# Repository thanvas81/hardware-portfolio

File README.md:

# Hardware Portfolio

PCB and embedded hardware projects by **Athanasios Vasiloglou**, Embedded Systems & Hardware Engineer.

Each project has 3D renders, schematics, layer views where available, and a write-up of the design. Projects are listed from most to least complex.

## At a glance

| # | Project | Area | Board | Key parts |
|---|---|---|---|---|
| 1 | [Industrial Controller / Gateway](industrial-controller-gateway/) | Industrial control | 4-layer · 340 × 147 mm · 486 parts | STM32H743, KSZ8863 Ethernet switch, isolated RS-485, mains AC/DC |
| 2 | [Linux SoM Carrier Board](linux-som-carrier-board/) | Industrial IoT | 4-layer · 167 × 100 mm · 274 parts | i.MX 91 SoM, EC25 LTE, Ethernet, RS-485, CAN |
| 3 | [Handheld High-Irradiance LED Controller](handheld-irradiance-system/) | Power electronics | 3 boards · Altium | USB-C PD, 2S charger, 4-switch buck-boost, nRF52840 |
| 4 | [GPS/GSM Tracker (Rev 3)](gps-gsm-tracker/) | IoT & tracking | 4-layer · 65 × 94 mm · 192 parts | STM32U575, LTE Cat-1, NEO-M9N GNSS |
| 5 | [BLE Channel Sounding Sensor Board](ble-channel-sounding-board/) | Wireless / thesis | 4-layer · 38 × 25 mm | nRF54L15, Channel Sounding, 17 cm mean error |
| 6 | [Vehicle I/O Validator (Rev 2)](vehicle-io-validator/) | Automotive test | 4-layer · 142 × 72 mm · 232 parts | STM32U545, 20 protected inputs, USB-C |
| 7 | [Compact LTE-M / NB-IoT Tracker](compact-lte-tracker/) | IoT & tracking | 4-layer · 49 × 53 mm · 89 parts | BG96, STM32U545, Li-ion charger |
| 8 | [Control Unit Tester (Rev 2)](control-unit-tester/) | Automotive test | 4-layer · 194 × 52 mm · 236 parts | Window comparators, 20 switched outputs |
| 9 | [RP2040 Diagnostic Tester (Rev 2)](rp2040-diagnostic-tester/) | Test tools | 2-layer · 69 × 54 mm | Raspberry Pi Pico, UART sniffer, 24 V input |
| 10 | [CANLink Module](can-link-module/) | Expansion module | 2-layer · 65 × 64 mm | PIC18 CAN controller, TCAN3413 |
| 11 | [Relay & Analog Input Expansion Board](relay-analog-io-board/) | Expansion module | 2-layer · 65 × 38 mm | TX2 relay, LMV324 analog front end |

---

## Featured projects

### [Industrial Controller / Gateway](industrial-controller-gateway/)

Mains-powered controller bridging a managed Ethernet switch to 24 V field I/O.

- STM32H743, KSZ8863 2-port Ethernet switch
- 2× isolated RS-485, 4–20 mA, PT100, opto inputs, relays, smart high-side outputs
- On-board 90 W AC/DC, four isolation domains, mains relay channel
- 4-layer, 340 × 147 mm, 486 components

`STM32H7` `Ethernet` `Isolation` `Mains` `KiCad`

<br clear="right">

---

### [Linux SoM Carrier Board](linux-som-carrier-board/)

Industrial IoT carrier for an NXP i.MX 91 Linux SoM. Full design and bring-up.

- Quectel EC25 LTE (mini-PCIe), dual SIM
- Ethernet, RS-485, CAN, USB-C, digital I/O, RTC, tamper input
- Wide-input supply, Li-ion backup with power-path
- 4-layer, 167 × 100 mm, 274 components

`i.MX 91` `Embedded Linux` `LTE` `KiCad` `Industrial IoT`

<br clear="right">

---

### [Handheld High-Irradiance LED Controller](handheld-irradiance-system/)

Battery-powered controller for a high-power red LED array. Freelance design across three boards.

- USB-C PD input, 2S Li-ion charger with power-path
- 4-switch buck-boost LED rail, 7 constant-current channels
- nRF52840 Bluetooth LE, IR temperature sensing, fan control

`Altium` `USB-C PD` `Power electronics` `nRF52840` `LED drivers`

<br clear="right">

---

### [GPS/GSM Tracker](gps-gsm-tracker/)

LTE Cat-1 + GNSS vehicle tracker, Rev 3 redesigned in KiCad for production.

- STM32U575 low-power MCU, SIMCom A7672 LTE modem, u-blox NEO-M9N GNSS
- Li-ion charger with power-path, wide-input buck, backup cell
- 4-layer, 65 × 94 mm, 192 components

`STM32U5` `LTE Cat-1` `GNSS` `KiCad` `4-layer`

<br clear="right">

---

### [BLE Channel Sounding Sensor Board](ble-channel-sounding-board/)

Custom nRF54L15 board for sub-metre indoor positioning with Bluetooth Channel Sounding. NTUA diploma thesis.

- **17 cm** mean ranging error across three anchors
- 4-layer, 38 × 25 mm PCB in KiCad
- Accelerometer + magnetometer, temperature / humidity / pressure
- USB-C or Li-ion, with charger and buck-boost

`nRF54L15` `Zephyr` `KiCad` `BLE` `Channel Sounding`

<br clear="right">

---

### [Vehicle I/O Validator](vehicle-io-validator/)

Test tool that monitors 20 vehicle I/O lines and reports them to a PC over USB.

- 20 protected inputs with red / blue status LEDs per channel
- STM32U545, USB-C, 60 V buck from the vehicle supply
- 4-layer, 142 × 72 mm, 232 components

`STM32U5` `Automotive` `Test equipment` `KiCad`

<br clear="right">

---

### [Compact LTE-M / NB-IoT Tracker](compact-lte-tracker/)

Small battery-backed asset tracker.

- Quectel BG96 (LTE-M / NB-IoT + GNSS), STM32U545
- Accelerometer wake-up, NOR flash logging
- Li-ion charger, wide-input buck, switched modem rail
- 4-layer, 49 × 53 mm, 89 components

`STM32U5` `LTE-M` `NB-IoT` `GNSS` `KiCad`

<br clear="right">

---

### [Control Unit Tester](control-unit-tester/)

Stand-alone, fully analog bench tester for vehicle control units.

- 16 inputs with window-comparator status LEDs
- 20 outputs, each switchable to +Vin / open / GND
- 60 V buck from the vehicle supply, no MCU needed
- 4-layer, 194 × 52 mm, 236 components

`Analog` `Automotive` `Test equipment` `KiCad`

<br clear="right">

---

## More boards

| | |
|:---:|:---:|
| <br>**[RP2040 Diagnostic Tester](rp2040-diagnostic-tester/)**<br>Raspberry Pi Pico field tool that talks to and sniffs UART links on 24 V equipment, with LCD and buttons | <br>**[CANLink Module](can-link-module/)**<br>Plug-in CAN ↔ UART bridge: PIC18 with on-chip CAN controller and TI TCAN3413 transceiver |
| <br>**[Relay & Analog Input Expansion Board](relay-analog-io-board/)**<br>Stack-on board with a relay output and protected, buffered analog inputs | |

---

[LinkedIn](https://www.linkedin.com/in/athanasios-vasiloglou-424599182/) · [GitHub profile](https://github.com/thanvas81)

<sub>Designs are shown for portfolio purposes only. Projects built for employers and clients are presented without source files, and are not licensed for reuse.</sub>

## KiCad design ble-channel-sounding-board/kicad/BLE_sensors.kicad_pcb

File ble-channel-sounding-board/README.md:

# BLE Channel Sounding Sensor Board

**Custom nRF54L15 board for sub-metre indoor positioning with Bluetooth Channel Sounding, plus environmental and motion sensing.**

Diploma thesis, School of Electrical and Computer Engineering, National Technical University of Athens (2025).
*Design of a Wireless Indoor Tracking System for Multi-Sensor Data Acquisition with BLE Channel Sounding*. Supervisor: Prof. E. Hristoforou.

<p align="center">
  
  &nbsp;
  
</p>

## Highlights

- **17 cm mean ranging error** across three anchors at 3–4.5 m, measured over a one-hour indoor capture
- **Bluetooth Channel Sounding** (Bluetooth 6.0) distance estimation using IFFT and phase-based ranging, instead of RSSI
- **4-layer, 38 × 25 mm PCB** designed in KiCad around the nRF54L15 SoC, with a continuous inner ground plane for RF performance
- **Multi-sensor**: 3-axis accelerometer + magnetometer (motion wake-up) and temperature / humidity / pressure
- **Portable power**: USB-C or single-cell Li-ion, with charger, power-path and buck-boost to a stable 3.3 V

## System overview

```mermaid
flowchart LR
    subgraph Tag["Tag (reflector) – this board"]
        S1["LSM303AH<br/>accel + magnetometer"] -->|SPI| MCU["nRF54L15<br/>(ME54BS01 module)"]
        S2["BME280<br/>temp / humidity / pressure"] -->|I²C| MCU
        PWR["USB-C / Li-ion<br/>charger + buck-boost"] --> MCU
    end
    subgraph Anchors["Anchors (initiators)"]
        A1["Initiator 1"]
        A2["Initiator 2"]
        A3["Initiator 3"]
    end
    MCU <-->|"BLE Channel Sounding"| A1 & A2 & A3
    MCU -->|"BLE advertising<br/>sensor data"| A1
    A1 & A2 & A3 -->|"UART → USB"| PC["Host PC<br/>logging & visualisation"]
```

## Hardware

| Block | Part | Notes |
|---|---|---|
| SoC / radio | Minew **ME54BS01** (Nordic **nRF54L15**) | BLE 6.0 Channel Sounding, integrated antenna |
| Motion | ST **LSM303AH** | 3-axis accelerometer + magnetometer on SPI, interrupt lines for motion wake-up |
| Environment | Bosch **BME280** | Temperature, humidity, pressure on I²C |
| Charger | Microchip **MCP73871** | Li-ion charging with power-path management and NTC input |
| Regulation | TI **TPS63031** buck-boost, TI **TLV70018** LDO | 3.3 V from 3.0–4.2 V battery or 5 V USB |
| USB | USB-C receptacle, Nexperia **PRTR5V0U2X** ESD, Microchip **MCP2221A** | USB-to-UART bridge for logging |
| Debug | Tag-Connect **TC2030** | SWD programming without a header |

Schematic is split into hierarchical sheets: power supply, charger, buck-boost, LDO, USB-C, USB-to-serial, temperature sensor, accelerometer/magnetometer.

**Files**

### PCB layers

4-layer stackup, 1.6 mm FR4: signals on the outer layers, a continuous ground plane on inner 1 for RF stability and clean return paths, and 3.3 V / 5 V power on inner 2.

| Top copper | Inner 1: ground plane |
|---|---|
|  |  |
| **Inner 2: power plane (3.3 V / 5 V)** | **Bottom copper** |
|  |  |

### Files

- [Schematic (PDF)](schematics/BLE_sensors_schematic.pdf)
- [Bill of materials](fabrication/BLE_sensors_BOM.xlsx)
- [Gerbers for fabrication](fabrication/BLE_sensors_gerbers.zip)
- [KiCad 9 project](kicad/): open `BLE_sensors.kicad_pro`

## Firmware

Written in C on **Zephyr RTOS / nRF Connect SDK** (source not included in this repository). Two roles:

**Tag (reflector)** – this board. Reads the sensors every 2 s, broadcasts them in non-connectable advertising, answers Channel Sounding requests, and sleeps when no motion is detected.

```mermaid
flowchart TD
    A["Start + init (BLE + sensors)"] --> B["Start advertising (CS reflector + data)"]
    B --> C["Every 2 s: read environment + battery"]
    C --> D["Send via non-connectable advertising"]
    B --> E["On connect → configure CS (reflector role)"]
    B --> G["Motion detected? → stay awake"]
    G --> H["No motion → sleep"]
    H --> I["Motion interrupt → wake & resume"]
```

**Anchor (initiator)**. Scans for the tag, connects, runs continuous Channel Sounding procedures, computes the distance and logs it over UART with the received sensor data.

```mermaid
flowchart TD
    A["Start → scan"] --> B{"Ranging peer?"}
    B -- no --> A
    B -- yes --> C["Connect → discover → CS capabilities"]
    C --> D["Configure CS + start continuous"]
    D --> E["Process ranging data"]
    E --> F["Log distance (2 s)"]
    F --> D
    C --> G["Subscribe custom data"]
    G --> H["Receive and log env/sensor data"]
    H --> G
```

## Results

Three initiators were mounted on the walls at 3.0 m, 4.0 m and 4.5 m from a stationary tag, and distances were logged for one hour.

| Anchor | Distance | Mean absolute error |
|---|---|---|
| Initiator 1 | 4.0 m | 0.142 m |
| Initiator 2 | 4.5 m | 0.177 m |
| Initiator 3 | 3.0 m | 0.193 m |
| **Overall** | | **0.171 m** |

<p align="center">
  
  &nbsp;
  
</p>

The IFFT-based estimator gave the most stable distance estimates. Full method and measurements are in the thesis.

## Documents

- [Thesis (PDF)](docs/thesis.pdf)
- [Presentation slides](docs/thesis_presentation.pptx)
- [Flowcharts (Mermaid sources)](docs/flowcharts/)

## Folder layout

```
images/        3D renders, copper layers, test setup, results
schematics/    schematic PDF
kicad/         KiCad 9 project (schematic sheets + PCB)
fabrication/   Gerbers and BOM
docs/          thesis, slides, flowchart sources
```

---

[← Back to all projects](../README.md)

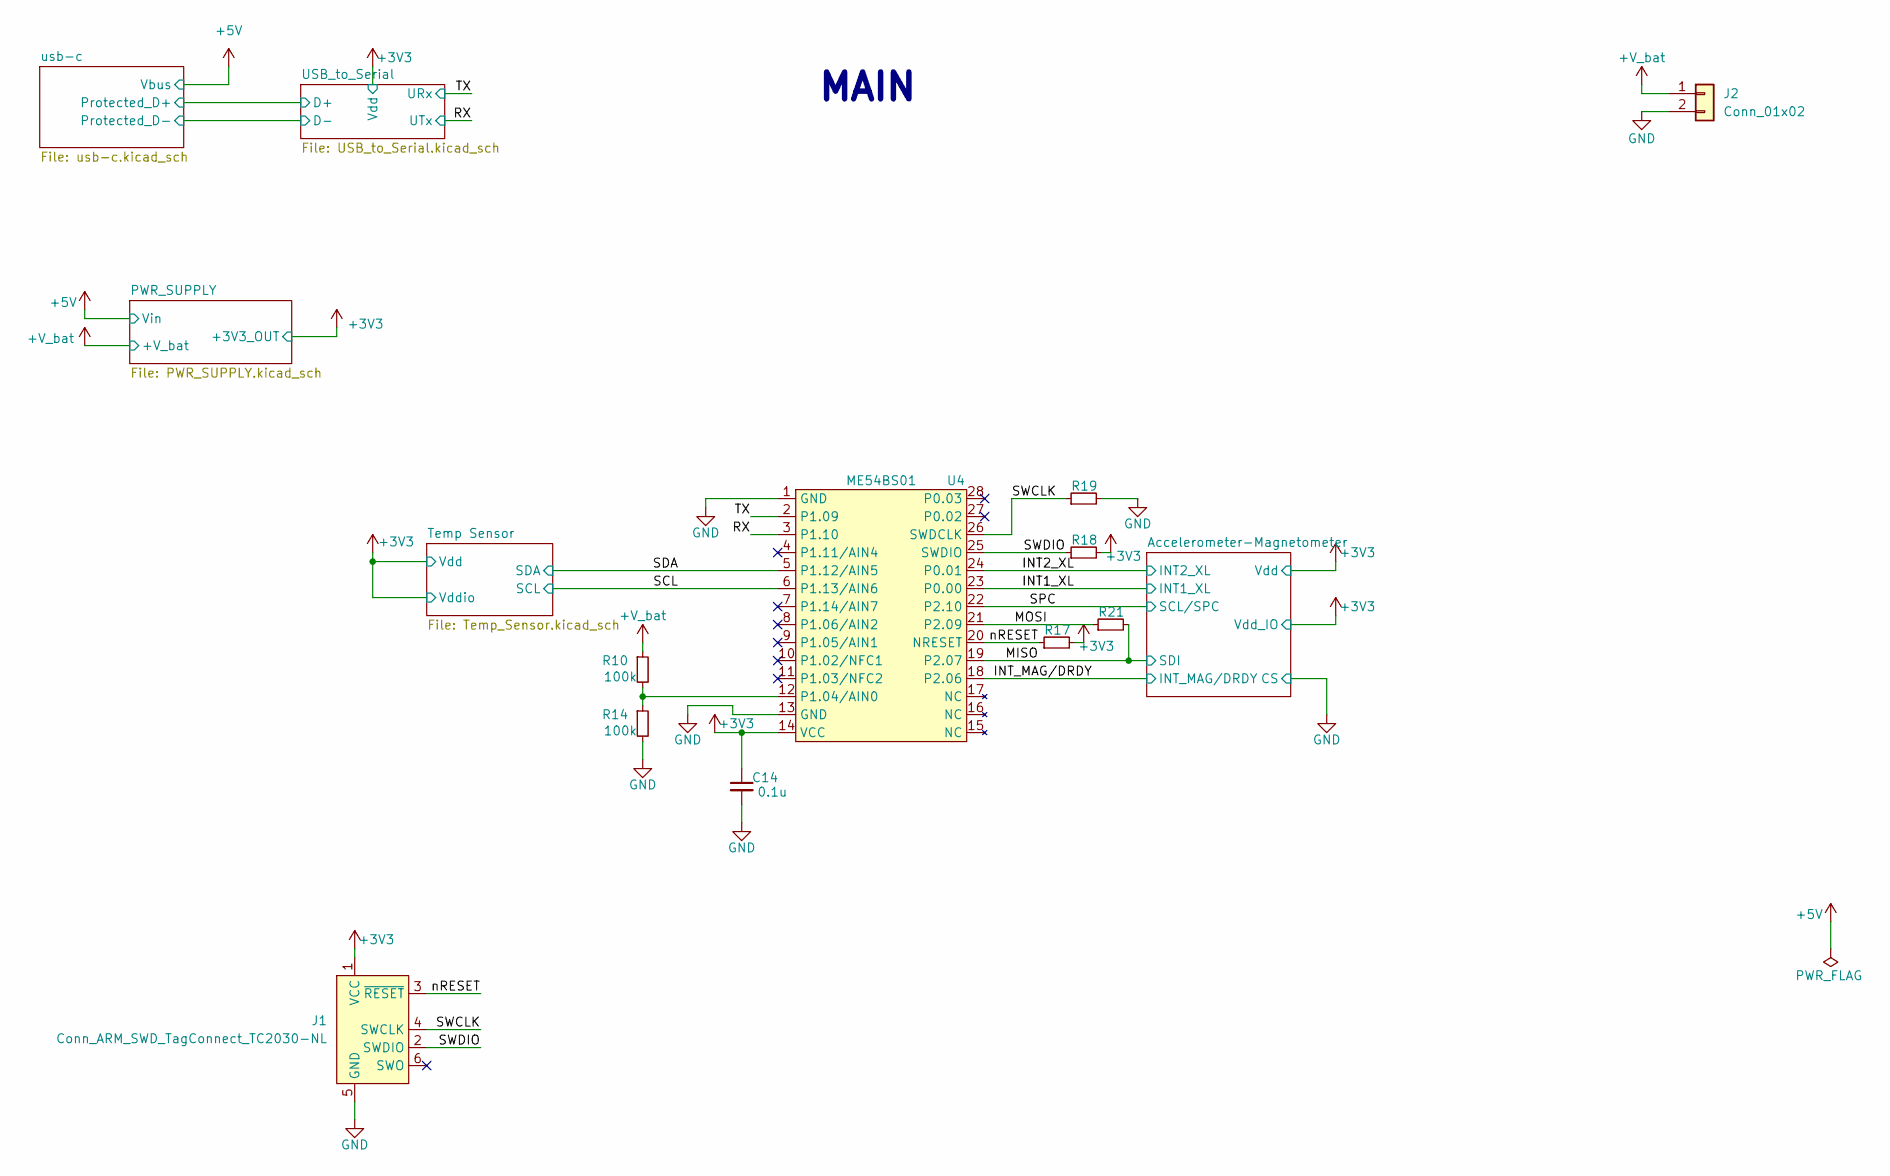
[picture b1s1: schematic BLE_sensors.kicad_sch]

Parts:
C14: 0.1u; C_0603_1608Metric
J1: Conn_ARM_SWD_TagConnect_TC2030-NL; Tag-Connect_TC2030-IDC-NL_2x03_P1.27mm_Vertical
J2: Conn_01x02; PinHeader_1x02_P1.27mm_Vertical
R10, R14: 100k; R_0603_1608Metric
R17, R18, R19, R21: 10k; R_0603_1608Metric
U4: ME54BS01

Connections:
+3V3: C14.1, J1.1 (VCC), R17.2, R18.2, U4.14 (VCC); also elsewhere on the board
+V_bat: J2.1, R10.1; also elsewhere on the board
/INT1_XL: U4.23 (P0.00); also elsewhere on the board
/INT2_XL: U4.24 (P0.01); also elsewhere on the board
/INT_MAG/DRDY: U4.18 (P2.06); also elsewhere on the board
/MISO: R21.2, U4.19 (P2.07); also elsewhere on the board
/MOSI: R21.1, U4.21 (P2.09)
/RX: U4.3 (P1.10); also elsewhere on the board
/SCL: U4.6 (P1.13/AIN6); also elsewhere on the board
/SDA: U4.5 (P1.12/AIN5); also elsewhere on the board
/SPC: U4.22 (P2.10); also elsewhere on the board
/SWCLK: J1.4 (SWCLK), R19.1, U4.26 (SWDCLK)
/SWDIO: J1.2 (SWDIO), R18.1, U4.25 (SWDIO)
/TX: U4.2 (P1.09); also elsewhere on the board
/nRESET: J1.3 (~RESET), R17.1, U4.20 (NRESET)
GND: C14.2, J1.5 (GND), J2.2, R14.2, R19.2, U4.1 (GND), U4.13 (GND); also elsewhere on the board
unnamed: R10.2, R14.1, U4.12 (P1.04/AIN0)

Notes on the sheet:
MAIN

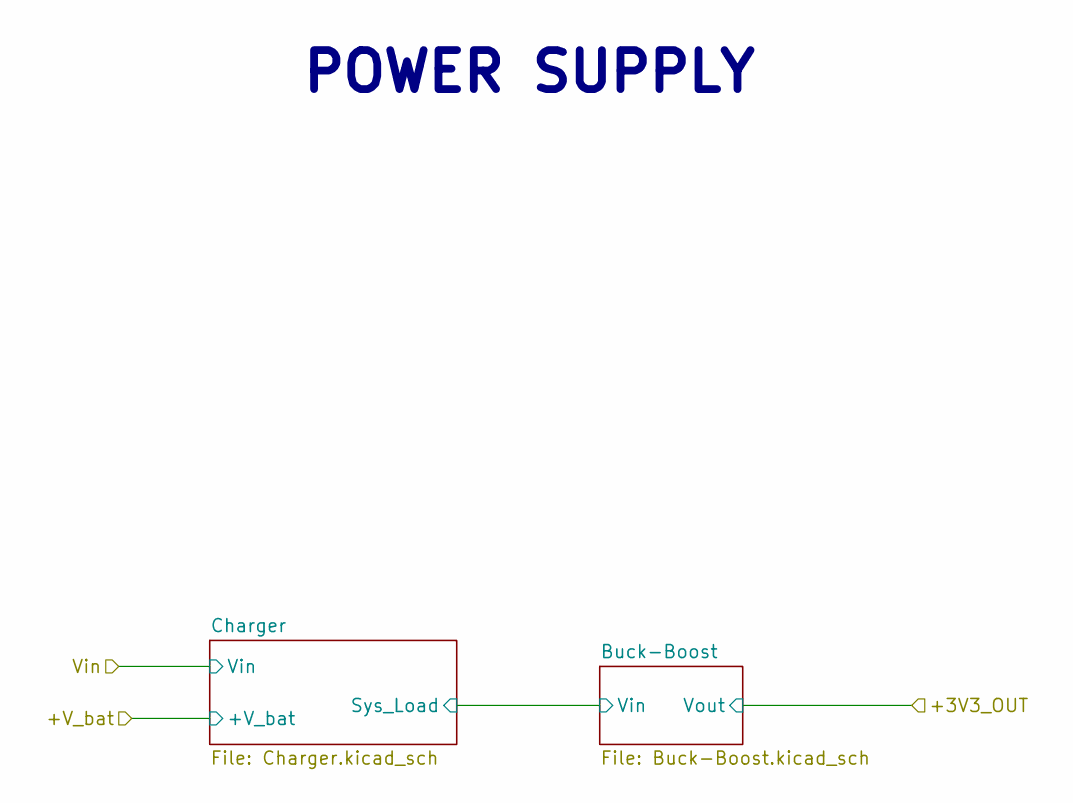
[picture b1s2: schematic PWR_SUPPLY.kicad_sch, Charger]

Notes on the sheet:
POWER SUPPLY

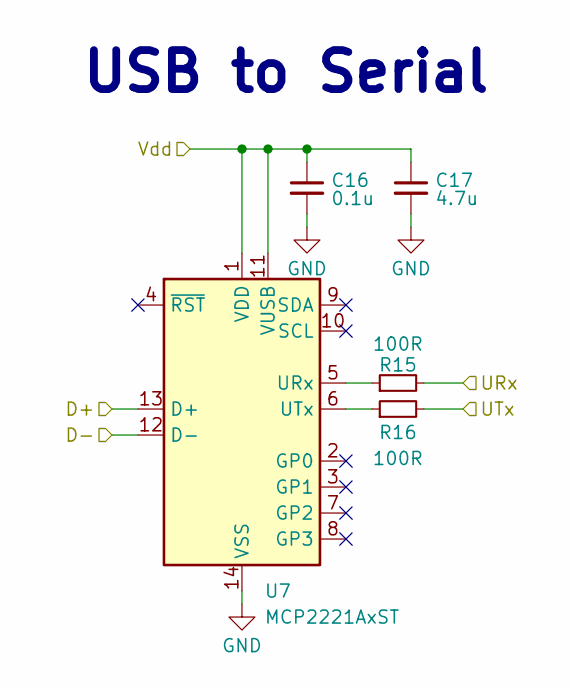
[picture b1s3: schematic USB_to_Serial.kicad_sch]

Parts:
C16: 0.1u; C_0603_1608Metric
C17: 4.7u; C_0805_2012Metric
R15, R16: 100R; R_0603_1608Metric
U7: MCP2221AxST; TSSOP-14_4.4x5mm_P0.65mm

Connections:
+3V3: C16.1, C17.1, U7.1 (VDD), U7.11 (VUSB); also elsewhere on the board
/RX: R16.2; also elsewhere on the board
/TX: R15.2; also elsewhere on the board
/usb-c/Protected_D+: U7.13 (D+); also elsewhere on the board
/usb-c/Protected_D-: U7.12 (D-); also elsewhere on the board
GND: C16.2, C17.2, U7.14 (VSS); also elsewhere on the board
unnamed: R15.1, U7.5 (URx)
unnamed: R16.1, U7.6 (UTx)

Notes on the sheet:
USB to Serial

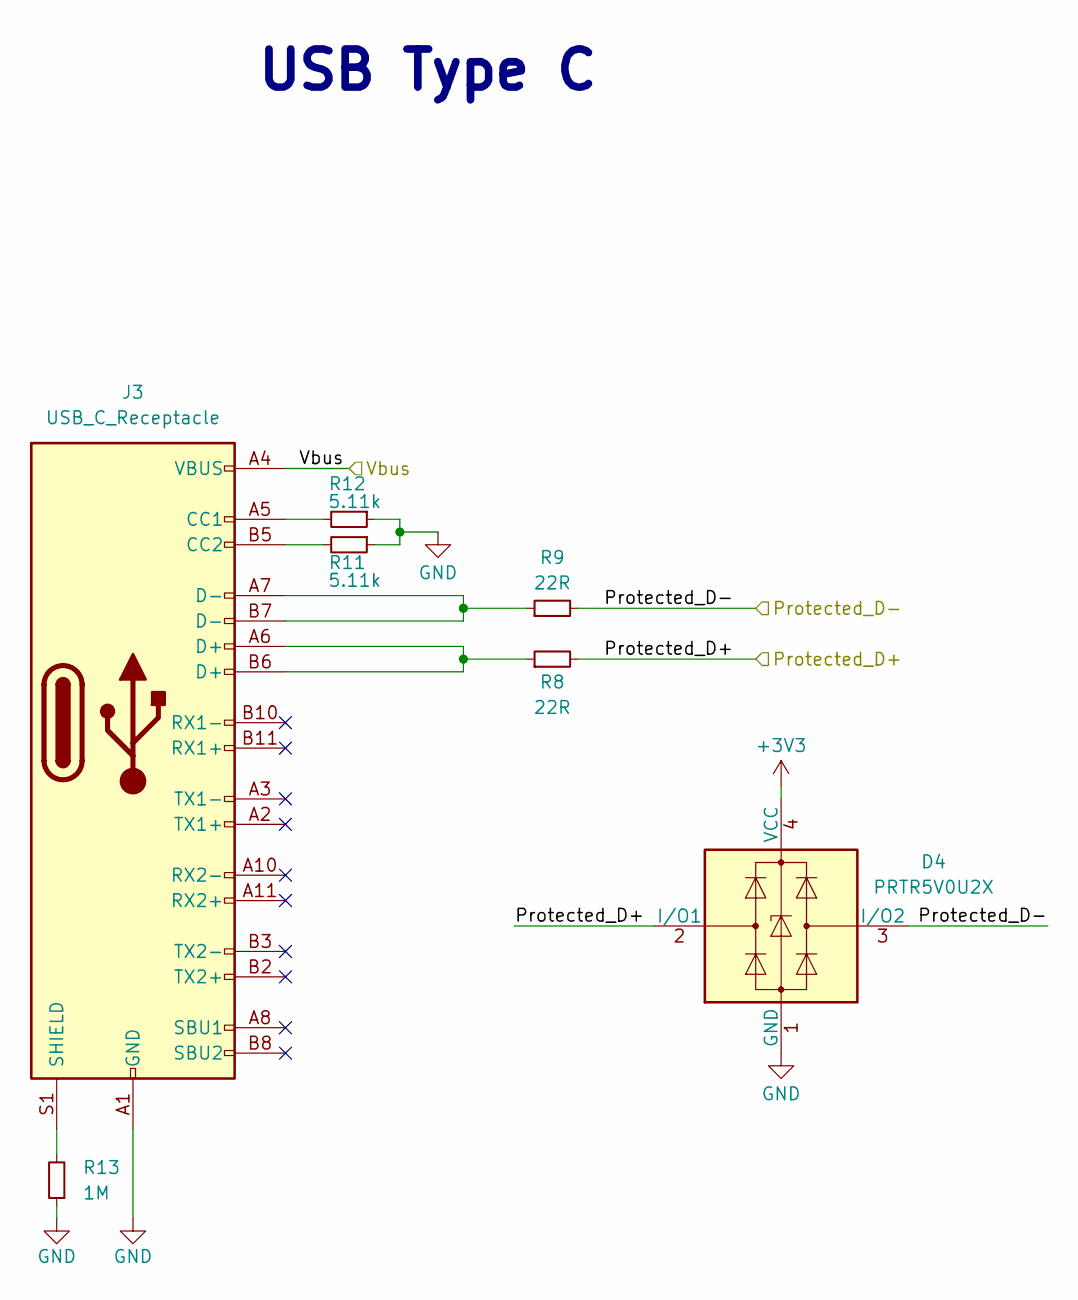
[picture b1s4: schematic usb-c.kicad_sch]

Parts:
D4: PRTR5V0U2X; SOT-143
J3: USB_C_Receptacle; USB_C_Receptacle_G-Switch_GT-USB-7010ASV
R8, R9: 22R; R_0603_1608Metric
R11, R12: 5.11k; R_0603_1608Metric
R13: 1M; R_0603_1608Metric

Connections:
+3V3: D4.4 (VCC); also elsewhere on the board
+5V: J3.A4 (VBUS), J3.A9 (VBUS), J3.B4 (VBUS), J3.B9 (VBUS); also elsewhere on the board
/usb-c/Protected_D+: D4.2 (I/O1), R8.2; also elsewhere on the board
/usb-c/Protected_D-: D4.3 (I/O2), R9.2; also elsewhere on the board
GND: D4.1 (GND), J3.A1 (GND), J3.A12 (GND), J3.B1 (GND), J3.B12 (GND), R11.1, R12.1, R13.1; also elsewhere on the board
unnamed: J3.A5 (CC1), R12.2
unnamed: J3.B5 (CC2), R11.2
unnamed: J3.A6 (D+), J3.B6 (D+), R8.1
unnamed: J3.A7 (D-), J3.B7 (D-), R9.1
unnamed: J3.S1 (SHIELD), R13.2

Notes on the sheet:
USB Type C

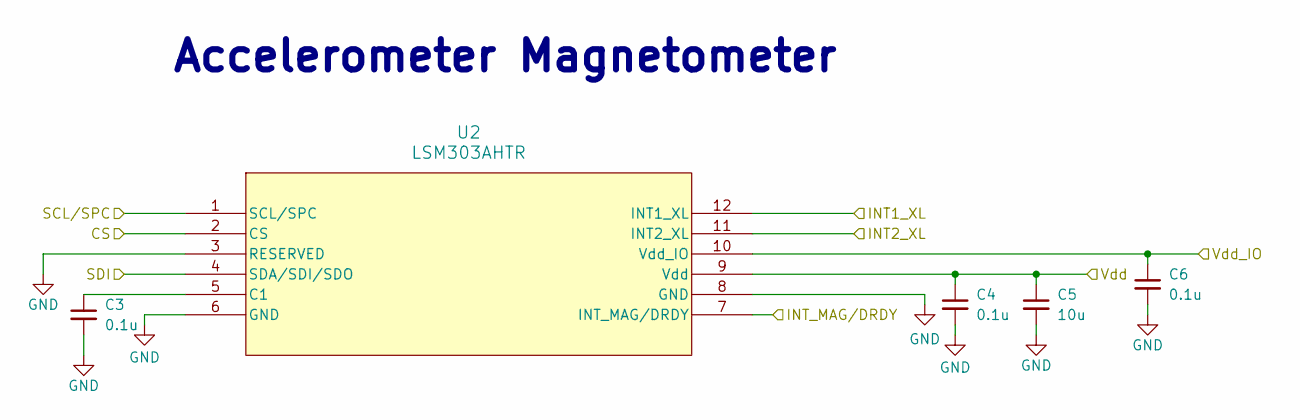
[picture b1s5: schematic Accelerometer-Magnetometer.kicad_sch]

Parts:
C3, C4, C6: 0.1u; C_0603_1608Metric
C5: 10u; C_0805_2012Metric
U2: LSM303AHTR

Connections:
+3V3: C4.1, C5.1, C6.1, U2.9 (Vdd), U2.10 (Vdd_IO); also elsewhere on the board
/INT1_XL: U2.12 (INT1_XL); also elsewhere on the board
/INT2_XL: U2.11 (INT2_XL); also elsewhere on the board
/INT_MAG/DRDY: U2.7 (INT_MAG/DRDY); also elsewhere on the board
/MISO: U2.4 (SDA/SDI/SDO); also elsewhere on the board
/SPC: U2.1 (SCL/SPC); also elsewhere on the board
GND: C3.2, C4.2, C5.2, C6.2, U2.2 (CS), U2.3 (RESERVED), U2.6 (GND), U2.8 (GND); also elsewhere on the board
unnamed: C3.1, U2.5 (C1)

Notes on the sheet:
Accelerometer Magnetometer

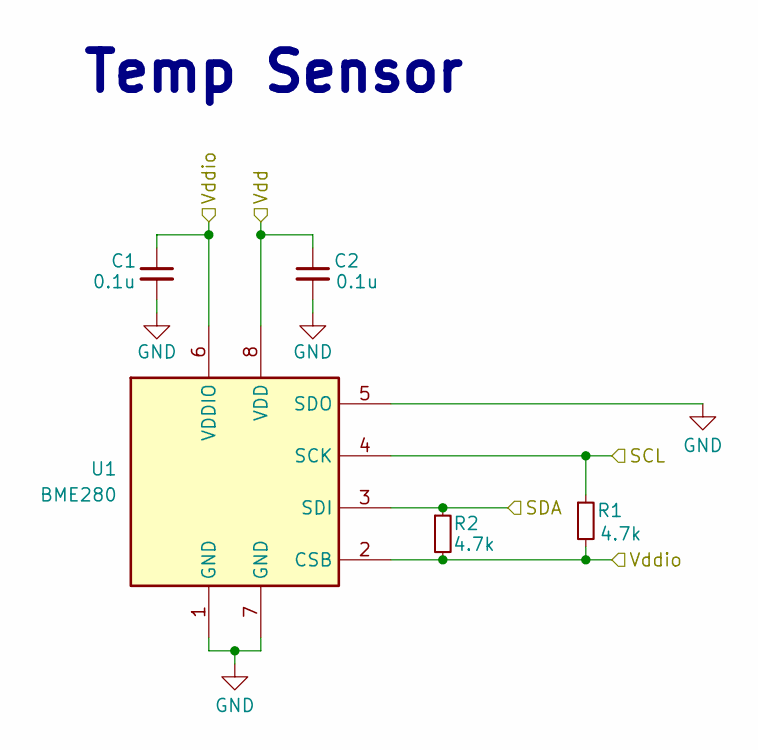
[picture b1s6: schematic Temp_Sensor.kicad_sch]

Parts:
C1, C2: 0.1u; C_0603_1608Metric
R1, R2: 4.7k; R_0603_1608Metric
U1: BME280; Bosch_LGA-8_2.5x2.5mm_P0.65mm_ClockwisePinNumbering

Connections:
+3V3: C1.1, C2.1, R1.2, R2.2, U1.2 (CSB), U1.6 (VDDIO), U1.8 (VDD); also elsewhere on the board
/SCL: R1.1, U1.4 (SCK); also elsewhere on the board
/SDA: R2.1, U1.3 (SDI); also elsewhere on the board
GND: C1.2, C2.2, U1.1 (GND), U1.5 (SDO), U1.7 (GND); also elsewhere on the board

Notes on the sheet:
Temp Sensor

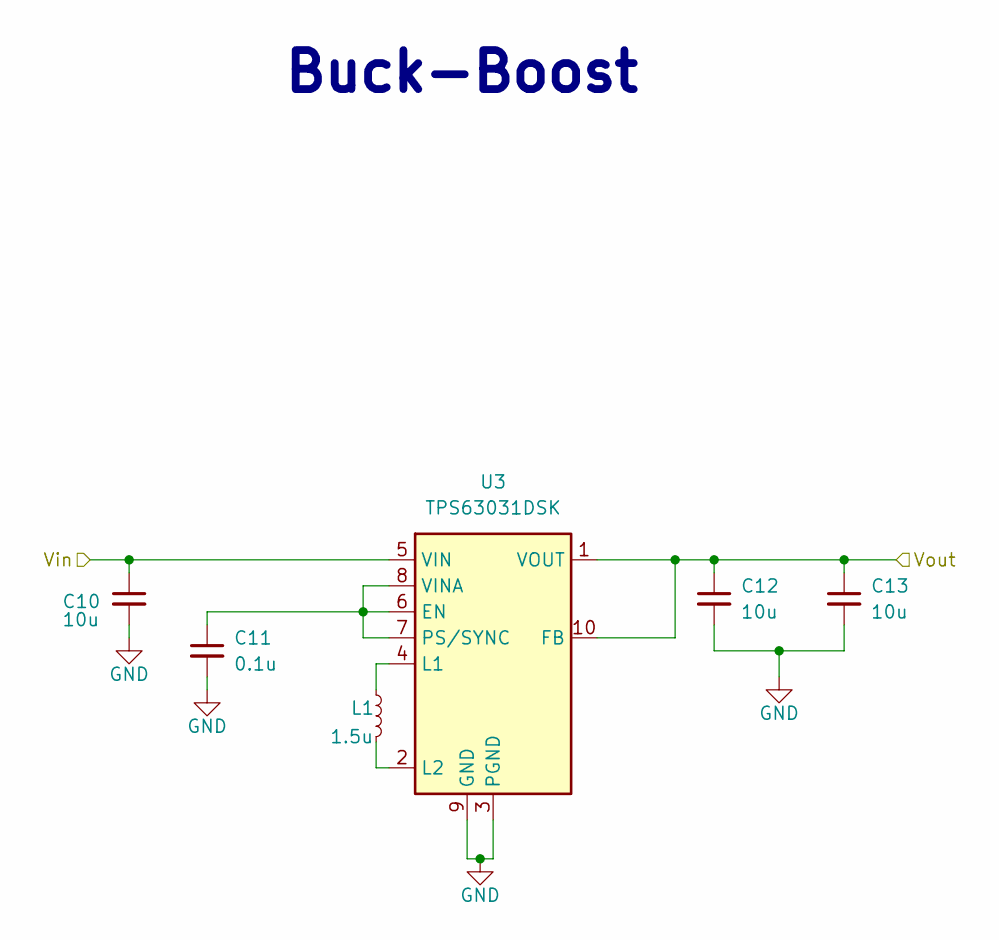
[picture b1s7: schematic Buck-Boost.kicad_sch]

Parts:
C10, C12, C13: 10u; C_0805_2012Metric
C11: 0.1u; C_0603_1608Metric
L1: 1.5u; L_1210_3225Metric
U3: TPS63031DSK; WSON-10-1EP_2.5x2.5mm_P0.5mm_EP1.2x2mm

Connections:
+3V3: C12.1, C13.1, U3.1 (VOUT), U3.10 (FB); also elsewhere on the board
/PWR_SUPPLY/Buck-Boost/Vin: C10.1, U3.5 (VIN); also elsewhere on the board
GND: C10.2, C11.2, C12.2, C13.2, U3.3 (PGND), U3.9 (GND), U3.11 (PGND); also elsewhere on the board
unnamed: C11.1, U3.6 (EN), U3.7 (PS/SYNC), U3.8 (VINA)
unnamed: L1.1, U3.4 (L1)
unnamed: L1.2, U3.2 (L2)

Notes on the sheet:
Buck-Boost

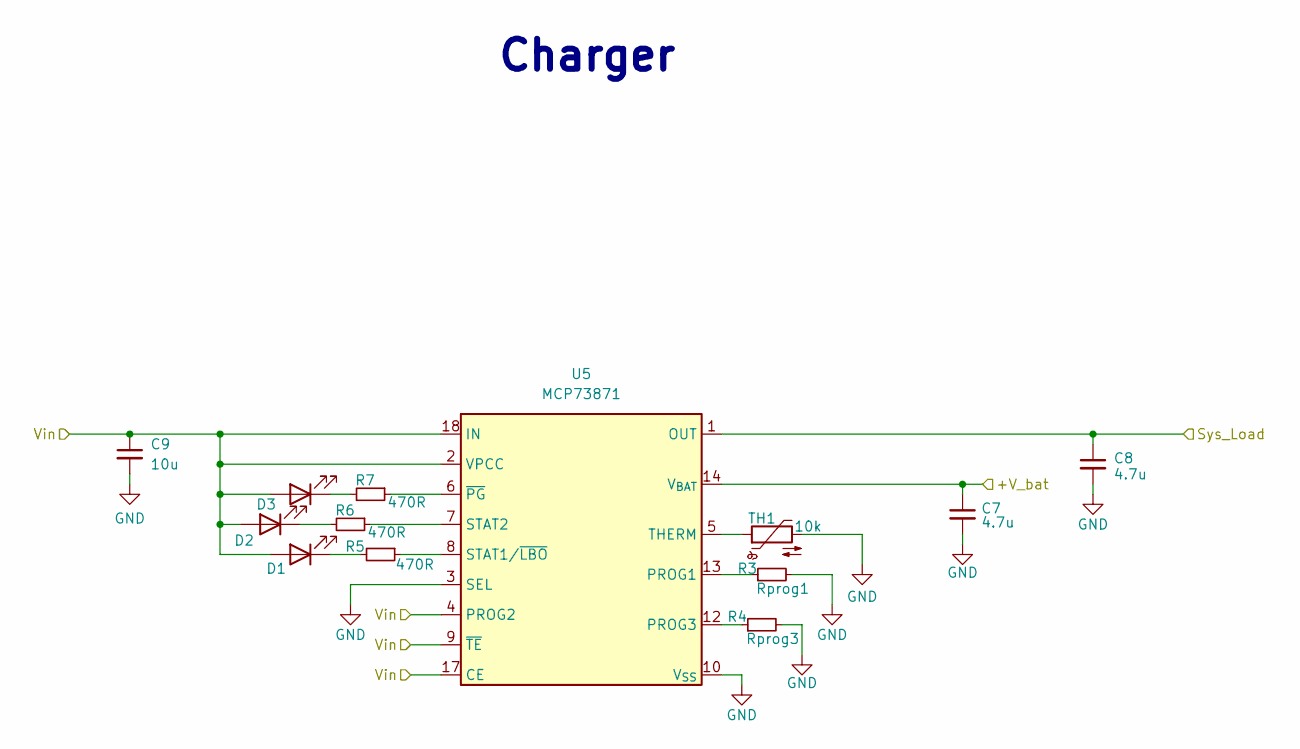
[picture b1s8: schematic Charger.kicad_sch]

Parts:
C7, C8: 4.7u; C_0603_1608Metric
C9: 10u; C_0603_1608Metric
D1, D2, D3: LED; LED_0603_1608Metric
R3: Rprog1; R_0603_1608Metric
R4: Rprog3; R_0603_1608Metric
R5, R6, R7: 470R; R_0603_1608Metric
TH1: 10k; R_0603_1608Metric
U5: MCP73871; QFN-20-1EP_4x4mm_P0.5mm_EP2.5x2.5mm

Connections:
+5V: C9.1, D1.2 (A), D2.2 (A), D3.2 (A), U5.2 (VPCC), U5.4 (PROG2), U5.9 (~TE), U5.17 (CE), U5.18 (IN), U5.19 (IN); also elsewhere on the board
+V_bat: C7.1, U5.14 (V_{BAT}), U5.15 (V_{BAT}), U5.16 (V_{BAT_SENSE}); also elsewhere on the board
/PWR_SUPPLY/Buck-Boost/Vin: C8.1, U5.1 (OUT), U5.20 (OUT); also elsewhere on the board
GND: C7.2, C8.2, C9.2, R3.2, R4.2, TH1.2, U5.3 (SEL), U5.10 (V_{SS}), U5.11 (V_{SS}), U5.21 (V_{SS}); also elsewhere on the board
unnamed: D1.1 (K), R5.2
unnamed: D2.1 (K), R6.2
unnamed: D3.1 (K), R7.2
unnamed: R3.1, U5.13 (PROG1)
unnamed: R4.1, U5.12 (PROG3)
unnamed: R5.1, U5.8 (STAT1/~LBO)
unnamed: R6.1, U5.7 (STAT2)
unnamed: TH1.1, U5.5 (THERM)
unnamed: R7.1, U5.6 (~PG)

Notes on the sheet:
Charger

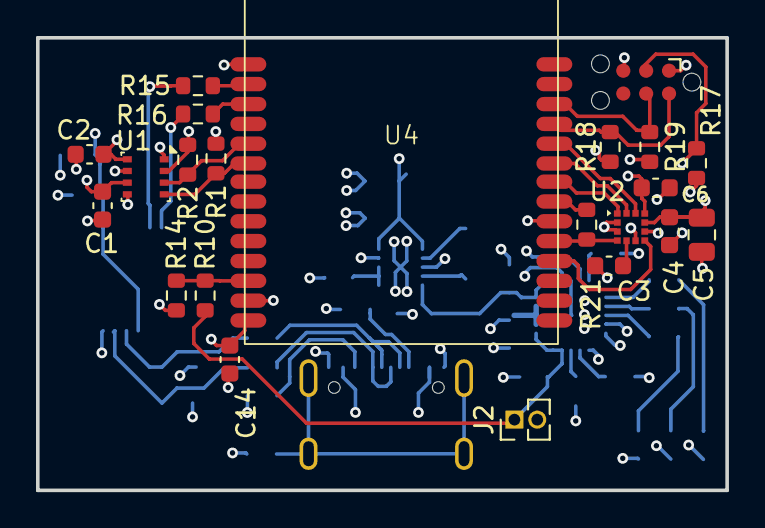
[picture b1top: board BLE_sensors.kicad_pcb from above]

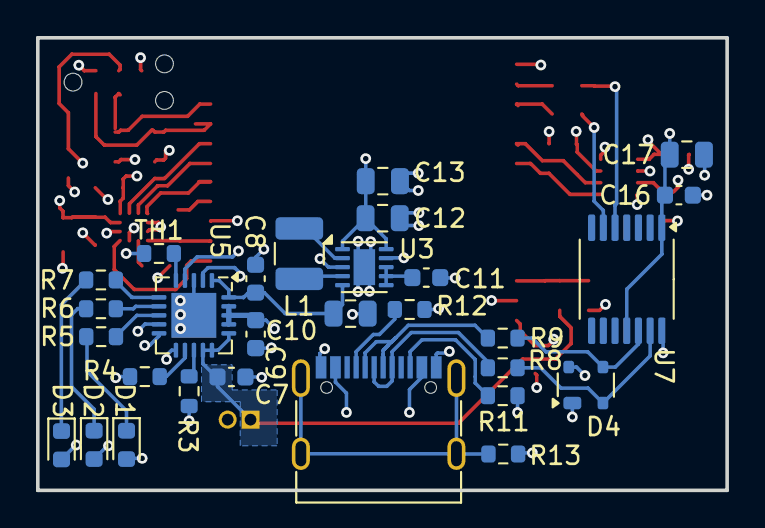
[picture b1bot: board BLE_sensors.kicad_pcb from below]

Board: 4 copper layers, 38.3 x 25.1 mm, 51 parts (29 on the bottom side), 41 nets.

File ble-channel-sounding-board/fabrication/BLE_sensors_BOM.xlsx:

Reference | Qty | Value | Footprint | Ordered | Status
C1, C2, C3, C4, C6, C11, C14, C16 | 8 | 0.1u | Capacitor_SMD:C_0603_1608Metric
C5, C10, C12, C13 | 4 | 10u | Capacitor_SMD:C_0805_2012Metric
C7, C8 | 2 | 4.7u | Capacitor_SMD:C_0603_1608Metric
C9 | 1 | 10u | Capacitor_SMD:C_0603_1608Metric
C17 | 1 | 4.7u | Capacitor_SMD:C_0805_2012Metric
D1, D2, D3 | 3 | LED | LED_SMD:LED_0603_1608Metric | OK
D4 | 1 | PRTR5V0U2X | Package_TO_SOT_SMD:SOT-143 | OK
J2 | 1 | Conn_01x02 | Connector_PinHeader_1.27mm:PinHeader_1x02_P1.27mm_Vertical
J3 | 1 | USB_C_Receptacle | Connector_USB:USB_C_Receptacle_G-Switch_GT-USB-7010ASV | GT-USB-7010ASV ?
L1 | 1 | 1.5u | Inductor_SMD:L_1210_3225Metric
R1, R2 | 2 | 4.7k | Resistor_SMD:R_0603_1608Metric
R3 | 1 | Rprog1 | Resistor_SMD:R_0603_1608Metric
R4 | 1 | Rprog3 | Resistor_SMD:R_0603_1608Metric
R5, R6, R7 | 3 | 470R | Resistor_SMD:R_0603_1608Metric
R8, R9 | 2 | 22R | Resistor_SMD:R_0603_1608Metric
R10, R14 | 2 | 100k | Resistor_SMD:R_0603_1608Metric
R11, R12 | 2 | 5.11k | Resistor_SMD:R_0603_1608Metric
R13 | 1 | 1M | Resistor_SMD:R_0603_1608Metric
R15, R16 | 2 | 100R | Resistor_SMD:R_0603_1608Metric
R17, R18, R19, TH1 | 4 | 10k | Resistor_SMD:R_0603_1608Metric
U1 | 1 | BME280 | Package_LGA:Bosch_LGA-8_2.5x2.5mm_P0.65mm_ClockwisePinNumbering | OK
U2 | 1 | LSM303AHTR | My_Libraries:LSM303AHTR | OK
U3 | 1 | TPS63031DSK | Package_SON:WSON-10-1EP_2.5x2.5mm_P0.5mm_EP1.2x2mm | OK
U4 | 1 | ME54BS01 | My_Libraries:ME54BS01 | OK | OK
U5 | 1 | MCP73871 | Package_DFN_QFN:QFN-20-1EP_4x4mm_P0.5mm_EP2.5x2.5mm | OK
U7 | 1 | MCP2221AxST | Package_SO:TSSOP-14_4.4x5mm_P0.65mm | ΟΚ
